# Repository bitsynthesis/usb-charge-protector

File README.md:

# USB Charge Protector

A simple USB adapter to prevent [juice jacking](https://en.wikipedia.org/wiki/Juice_jacking)
by breaking the data connection between the charger and device. Includes an
an optional power indicator LED.

Project created with [Kicad 5](http://www.kicad-pcb.org).

\
PCB

\
Front

\
Back

\
In use

# DEFCON 29 Assembly Notes

The power indicator LED is not essential, but needs to be properly oriented to function. When looking at the back of the board as outlined below, put the LED in the top location with the green side (cathode) pointing to the right.
```
| \_
|
|  _
| /
```
Or just look up the pinout on the USB jacks to determine which pin is power and which is ground :)

# License

Copyright Ben Baker-Smith 2019.

This documentation describes Open Hardware and is licensed under the
[CERN OHL v.1.2](/LICENSE.TXT).

You may redistribute and modify this documentation under the terms of the
CERN OHL v.1.2. This documentation is distributed
WITHOUT ANY EXPRESS OR IMPLIED WARRANTY, INCLUDING OF
MERCHANTABILITY, SATISFACTORY QUALITY AND FITNESS FOR A
PARTICULAR PURPOSE. Please see the CERN OHL v.1.2 for applicable
conditions

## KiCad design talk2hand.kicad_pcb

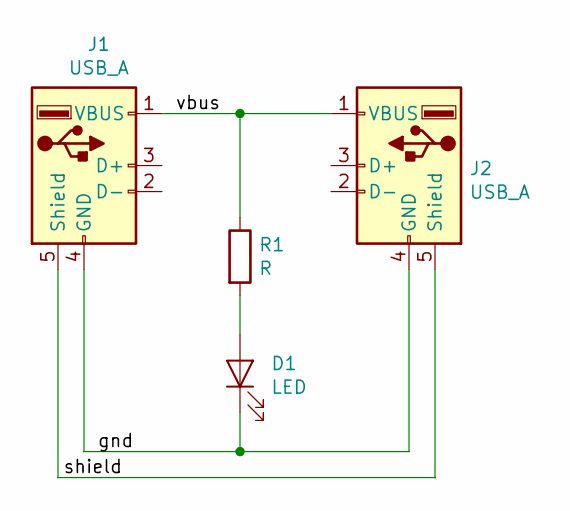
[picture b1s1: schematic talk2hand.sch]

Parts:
D1: LED; LED_0603_1608Metric_Pad1.05x0.95mm_HandSolder
J1, J2: USB_A; USB_A_Stewart_SS-52100-001_Horizontal
R1: R; R_0603_1608Metric_Pad1.05x0.95mm_HandSolder

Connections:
/gnd: D1.1 (K), J1.4 (GND), J2.4 (GND)
/shield: J1.5 (Shield), J2.5 (Shield)
/vbus: J1.1 (VBUS), J2.1 (VBUS), R1.1
unnamed: D1.2 (A), R1.2

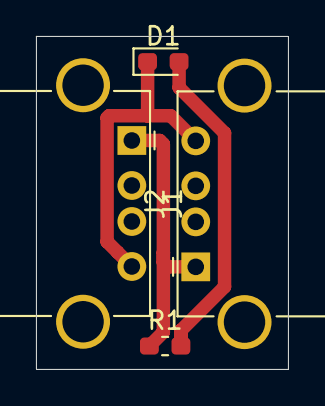
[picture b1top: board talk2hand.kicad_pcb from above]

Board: 2 copper layers, 14.0 x 18.5 mm, 4 parts (0 on the bottom side), 4 nets.

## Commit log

2019-09-21 Init
2019-10-15 PCB updates
2019-10-18 Images for docs
2019-10-20 Preparation for release
    - Rename to USB Charge Protector
    - Add license
    - Add README
    - Add CHANGELOG
2021-08-06 LED assembly notes
